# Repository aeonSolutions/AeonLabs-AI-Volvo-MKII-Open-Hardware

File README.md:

[ ](https://discord.gg/hw3j3RwfJf)

<p align="center">
    <br>

 &nbsp;

**[More Stats](https://github.com/aeonSolutions/AeonLabs-AI-Volvo-MKII-Open-Hardware/wiki/Project-Statistics)**
</p>

**Navigation** | [AeonLabs Main Index](https://github.com/aeonSolutions/aeonSolutions/blob/main/aeonSolutions-Main-Index.md)  >>  [Open Hardware Electronics](https://github.com/aeonSolutions/PCB-Prototyping-Catalogue)  >>   [Vehicle Automation](https://github.com/aeonSolutions/PCB-Prototyping-Catalogue/tree/main/Vehicle%20Automation)  >> Volvo P2 Open Hardware

<div align="right">
    
 <a href="https://github-com.translate.goog/aeonSolutions/AeonLabs-AI-Volvo-MKII-Open-Hardware/wiki?_x_tr_sl=en&_x_tr_tl=pt&_x_tr_hl=en&_x_tr_pto=wapp">Change language</a> <br>
 Last update: 24-06-2024
</div>

# Open Hardware Electronics for the Volvo P2 platform
**current project Total: > 1350 work.h** <br>
<sup>Status: Ongoing Project </sup> <br>
[where to buy](https://github.com/aeonSolutions/PCB-Prototyping-Catalogue/wiki/Where-to-Buy) already assembled and ready to use.

⚠️ This project is delayed because all my tools and equipment including all the Volvo P2 modules and wiring got stolen from my workplace and apartment ⚠️

**The problem** <br>
&nbsp; Nowadays, repairing hardware electronics is impossible or almost impossible. Current practice forces a car owner to replace instead of repair. This has a really high cost and pushes owners to seek other less trustworthy solutions using components used in other vehicles. Since this type of component is nowadays heavily protected, maintenance and repair outside the official car manufacturer authorized dealer to pose additional risks every time a piece of hardware electronics or firmware requires reverse engineering and modification just to enable it and make it work in another vehicle. Furthermore, recurrently found good, fully functional cars, with the highest safety classification rating on their chassis, the [Euro NCAP 5 star rating](https://www.euroncap.com/en/about-euro-ncap/how-to-read-the-stars/) being sent to the scrap yard due to outdated electronics and components and a too low insurance valuation that limits repairability of the vehicle.    

**Summary** <br>
The overall objective of this open project is to extend the life of vehicles by means of updating them to current EU standards namely safety regulations and emission pollutants. As so vehicles undergo a process of refurbishment service and full-featured overhaul of technology updates from mechanical key components to the interior habitacle, comfort, and safety of a vehicle. Branded **Auto RFTI™** (refurbishment, facelift, and technology improvements) goes a step further than just a vehicle facelift and will differentiate by offering simple & easy hardware electronics and components for extending vehicle utilization life by means of technology upgrades to improve safety while at the same time reduce vehicle emissions. 
- [The 6 Levels of Vehicle Autonomy](https://github.com/aeonSolutions/AeonLabs-AI-Volvo-MKII-Open-Hardware/wiki/The-6-Levels-of-Vehicle-Autonomy)
- [Milestones to Achieve for the Open Hardware Electronics](https://github.com/aeonSolutions/AeonLabs-AI-Volvo-MKII-Open-Hardware/wiki/Milestones-to-Achieve--for-the-Open-Hardware-Electronics)

<br>

In one sentence: 
<div align="center">

***"I'm solving all the electronics issues that make a P2 Volvo have a bad reputation"*** <br>

</div>

**Proof-of-Concept** <br>
&nbsp; Design and prototype OEM hardware electronics capable of the same operation and functionality for all Volvo's with the [common chassis P2](https://en.wikipedia.org/wiki/Volvo_P2_platform), period 1998 to 2009 (S80, S60, V70 XC70, XC90), using the existing wiring on those cars (backward compatible). Instead of using closed and protected logic, it uses open hardware and open firmware hardware electronics as a direct replacement for existing* wiring in a vehicle, in particular older cars. This will facilitate repeatability and maintenance on any "repair shop" outside authorized dealers and requires no reverse engineering and no modification to make it work in a vehicle.<br>

&nbsp; To achieve this task I will be using the electronics and electrical wiring of a donor car I already have. This will serve as a ground base to commercialize automotive solutions using an open business logic (open hardware and open software) for other car brands and models. Including LPG systems.

<div align="center">

***"still.... even if it is not easily possible ...it will definitely going to be AWESOME running a car <br> that will meet the latest EURO emissions except on the pink slip"*** <br>
<sup> <a href="https://discordapp.com/channels/879495735912071269/937480820594208808/1203010918833721446">Discord Server of Speeduino 02-02-2024 </a> </sup>
</div>

&nbsp; Since this is an open hardware project, the main selection of choice for the operating system will be Android Auto for the main LCD screen, in the center console. Nowadays there is a plenitude of "open auto" solutions using Raspberry Pi. I'll be designing the hardware electronics made to fit an SoC module, and I'll be starting with NVidia's Jetson Nano. In the following YouTube video, there's a good example of a traditional media unit https://www.youtube.com/watch?v=RgbHXTHUnQw <br>

Read more about ...
- [Open Hardware Design Considerations](https://github.com/aeonSolutions/AeonLabs-AI-Volvo-MKII-Open-Hardware/wiki/Open-Hardware-Design-Considerations)
- [Firmware Programming](https://github.com/aeonSolutions/AeonLabs-AI-Volvo-MKII-Open-Hardware/wiki/Firmware-Programming)

<br>

There are now 2 ways to navigate my hardware electronics catalog. The icons below will take you  to another page where this catalog is displayed using a conventional landing page design & styling. If you like code and more technical information, browse this page instead.
 
The icon to the left is suited to all those users who are only looking for a solution to a problem and not into the real technical details.  The icon to the right will take you directly to a webpage with all hardware electronics currently at the [M.V.P. stage](https://en.wikipedia.org/wiki/Minimum_viable_product). If you're not into technical information and are here only to buy, this is the option for you. 

<p align="center">
 
  &emsp;&emsp;&emsp;&emsp;&emsp;&emsp;&emsp;
   <br>
 <sup>View this repository in a conventional landing page</sup>
  &emsp;&emsp;&emsp;&emsp;&emsp;&emsp;&emsp;
 <sup> View all open hardware solutions ready to buy, install, and use</sup>
</p>

Make sure you also view my **Open Source Software Catalogue** [here](https://github.com/aeonSolutions/aeonlabs-open-software-catalogue). 

<br>

## What hardware electronics will be conceptualized, prototyped, and tested
&nbsp; The main objective of this project is to study the advantages of using open solutions and compare them with conventional hardware electronics solutions. In particular in regards to serviceability, maintenance, and repairability and also importantly, in regards to personal ownership safety. While driving and while parked (thieves). 

[continue reading ...](https://github.com/aeonSolutions/AeonLabs-AI-Volvo-MKII-Open-Hardware/wiki)

<br>

## Compatibility

<p align="center">

</p>

<br>

**Get a Notification on every PCB update**

|  | You can fill in your [email here (Google form)](https://docs.google.com/forms/d/e/1FAIpQLScErMgQYRdA-umvCjvTPPrCO7Lg1QYowTxb7vfa8cTfrcPEAA/viewform?usp=pp_url) and I'll send a reminder when a new PCB prototype is made available here or a new revision for an existing PCB. Stay tuned! |
|-------------|------|

<br>

**Hire AeonLabs** <br>
If you like my work here and are looking to design and deploy your own smart device find [here](https://github.com/aeonSolutions/PCB-Prototyping-Catalogue/wiki/How-to-Hire-AeonLabs) how to hire me. 

<br>

## Join the Beta Program
Join the beta program to test and debug to provide feedback, ideas, modifications, suggestions, and improvements. And in return, write your own article blog, or post on social media about it. See participation conditions on the [Wiki](https://github.com/aeonSolutions/PCB-Prototyping-Catalogue/wiki/Beta-Participation-Agreement).  

## Contributing

Bug reports and pull requests are welcome on any of AeonLabs repositories. This project is intended to be a safe, welcoming space for collaboration, and contributors are expected to adhere to the [code of conduct](https://github.com/aeonSolutions/OpenScience-Dataverse-API-C-library/blob/main/CODE_OF_CONDUCT.md).

- Contributing
  - [Your Contributions Matter](https://github.com/aeonSolutions/PCB-Prototyping-Catalogue/wiki/Your-Contributions-Matter)
  - [Contributor Code of Conduct](https://github.com/aeonSolutions/PCB-Prototyping-Catalogue/wiki/Contributor-Code-of-Conduct)

<br>

**[Beta Participation Agreement](https://github.com/aeonSolutions/PCB-Prototyping-Catalogue/wiki/Beta-Participation-Agreement)**

The Beta Participant Agreement is a legal document being executed between you and AeonLabs that outlines the conditions when participating in the Beta Program.

## Coding standards

Please make sure tests pass before committing, and add new tests for new additions.

- Licensing 
  - [AeonLabs Solutions for Open Hardware & Source Development](https://github.com/aeonSolutions/PCB-Prototyping-Catalogue/wiki/AeonLabs-Solutions-for-Open-Hardware-&-Source-Development)

<br>
<br>

## Author

You can get in touch with me on my LinkedIn Profile:

#### Miguel Tomas

You can also follow my GitHub Profile to stay updated about my latest projects: 

<br>

### Be supportive of my dedication and work towards technology education and buy me a cup of coffee
The PCB Design Files I provide here for anyone to use are free. If you like this Smart Device or use it, please consider buying me a cup of coffee, a slice of pizza, or a book to help me study, eat, and think new PCB design files.

<p align="center">
    
</p>

### Make a donation on Paypal
Make a donation on PayPal and get a TAX refund*.

<p align="center">
    
</p>

### Support all these open hardware projects and become a GitHub sponsor  
Did you like any of my PCB KiCad Designs? Help and Support my open work to all by becoming a Github sponsor.

<p align="center">

</p>

## License

Before proceeding to download any of AeonLab's open-source code for software solutions and/or open hardware electronics for smart devices and data acquisition make sure you are choosing the right license for your project. See [AeonLabs Solutions for Open Hardware & Open Source Code](https://github.com/aeonSolutions/aeonSolutions/wiki/AeonLabs-Licensing) for more information. For commercial business solutions contact AeonLabs ℹ️ using the contacts above. Thank you 🙏.

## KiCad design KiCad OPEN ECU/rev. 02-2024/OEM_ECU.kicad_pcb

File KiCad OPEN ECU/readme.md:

[Main Page](https://github.com/aeonSolutions/AeonLabs-AI-Volvo-MKII-Open-Hardware/wiki)  >>  KiCad project files for the OPEN ECU

<div align="right">
 <a href="https://github-com.translate.goog/aeonSolutions/AeonLabs-AI-Volvo-MKII-Open-Hardware/wiki?_x_tr_sl=en&_x_tr_tl=pt&_x_tr_hl=en&_x_tr_pto=wapp">Change language</a>  <br>
Last change 09-04-2024
</div>

<br>

This folder contains the KiCad Project files, for the hardware electronics of the OPEN ECU.  Each KiCad project is available with a [creative commons share alike non-commercial license](https://creativecommons.org/licenses/by-nc-sa/4.0/deed.en). 

<p align="center">
  <strong> <a href="https://aeonsolutions.github.io/portfolio/hardware_electronics/automotive/">Interactive web view of the PCB Layout</a> </strong> <br>
 <sup>Click to view the latest revision of the PCB Layout</sup>
</p>

However, they're not fully complete. If you like it and are looking to use it on your projects, you can download the complete Kicad project files with a one-time donation, [click here](https://github.com/sponsors/aeonSolutions) to learn how,  and don't forget to include it in a message the name of the module/hardware electronics you need. <br> Thank you 🙏.

### Support all these open hardware projects and become a GitHub sponsor  
Did you like any of my PCB KiCad Designs? Help and Support my open work to all by becoming a GitHub sponsor.

<p align="center">

</p>

#

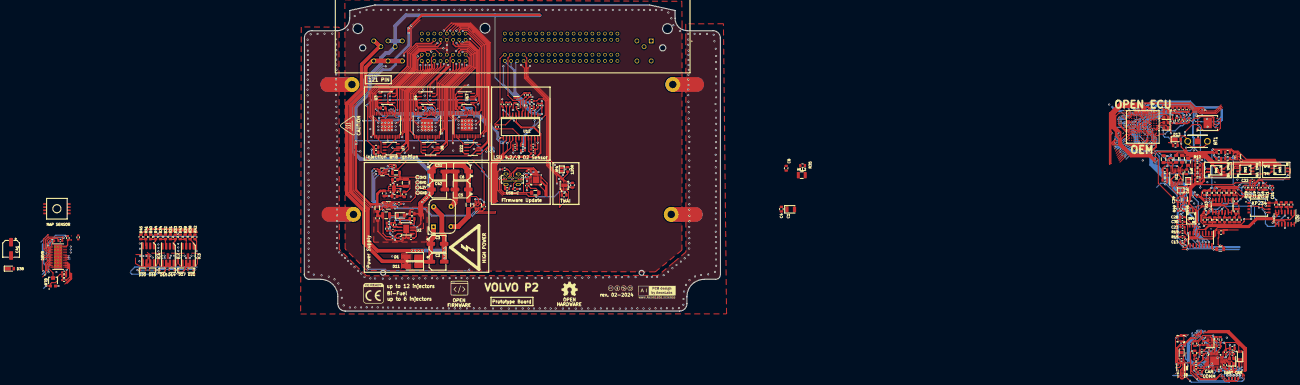
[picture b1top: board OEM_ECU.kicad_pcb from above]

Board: 2 copper layers, 168.9 x 124.3 mm, 246 parts (1 on the bottom side), 206 nets.

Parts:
AUC1: 100nF; C_0603_1608Metric
AUR1: AUR9718x_DFN_3x3mm_6_pin; AUR9718 ST1S09 SON95P300X300X100-7N
AUR_C1: 22uF; C_0805_2012Metric_Pad1.18x1.45mm_HandSolder
AUR_C2: 4.7uF; C_0805_2012Metric_Pad1.18x1.45mm_HandSolder
AUR_R1: 24k; R_0805_2012Metric_Pad1.20x1.40mm_HandSolder
AUR_R2: 75k; R_0805_2012Metric_Pad1.20x1.40mm_HandSolder
AUR_l1: 3.3uF; L_1210_3225Metric
BT1: Battery_Cell; pcb battery 3 pin
C1, C7, C8, C8#2, C11, C12, C16, C17, C27, C33, C37: 0.1uF; C_0805_2012Metric
C2, C42: 100pF; CP_Elec_6.3x7.7
C3, C5, C6: 10uF; CP_Elec_6.3x7.7
C4: 47uF; CP_EIA-3528-21_Kemet-B
C10, C26, C38: 1uF; C_0805_2012Metric
C13, C23: 270nF; C_0603_1608Metric
C14, C15, C20: 0.22uF; C_0805_2012Metric
C18, C19, C29: 0.1uF; C_0603_1608Metric
C21, C22: 0.22uF; C_0603_1608Metric
C24: 100uF; C_1206_3216Metric
C25, C35, C39, C40: 0.01uF; C_0805_2012Metric
C28: 0.01uF; C_0603_1608Metric
C30: 4700pF; C_0603_1608Metric
C32: 4.7uF; CP_Elec_6.3x7.7
C34, C36: 1nF; C_0805_2012Metric
C41: 100uF; CP_Elec_6.3x7.7
CHC1, CHC2, CHC3: 1uF; C_0603_1608Metric
CJC1: 2.2nF; C_0603_1608Metric
CJC2, CJC3, CJC4, CJC5, CJC6: 100nF; C_0603_1608Metric
CJC7, CJC8: 33nF; C_0603_1608Metric
CJQ1: AO3400A; SOT-23
CJR1: 61R9; R_0603_1608Metric
CJR2: 10K; R_0603_1608Metric
CJR3: 300R; R_0603_1608Metric
CJR4: 31K6; R_0603_1608Metric
CJR5, CJR11: 4K7; R_0603_1608Metric
CJR6, CJR8, CJR10: 100K; R_0603_1608Metric
CJR7: 470K; R_0603_1608Metric
CJR9: 6K8; R_0603_1608Metric
D1, D11: SS36; D_SMA_Handsoldering
D13, D38: D_Schottky; D_PowerDI-123
D14, D15, D16, D17, D20, D21: D; D_SOD-323
DRV8: DRV8825PWPR
DRVC1: 10nF; C_0603_1608Metric
DRVC2: 100nF; C_0603_1608Metric
DRVC3: 0.47uF; C_0603_1608Metric
DRVR1: 1K5; R_0603_1608Metric
DRVR2: 10K; R_0603_1608Metric
DRVR3, DRVR4: 0.10R; R_0603_1608Metric
EC1, EC8, EC9, EC14, EC15, EC17: 100nF; C_0603_1608Metric
EC2, EC3, EC4, EC5: 22pF; C_0603_1608Metric
EC6, EC7: 10uF; C_0805_2012Metric
EC16: 1uF; C_0805_2012Metric
ECY1: 32.768Mhz; Crystal_SMD_3225-4Pin_3.2x2.5mm
ECY2: 40Mhz; Crystal_SMD_3225-4Pin_3.2x2.5mm
ER1, ER3: 10k; R_0603_1608Metric
ER2: 499R; R_0603_1608Metric
ER4, ER5, ER6: 1R; R_1206_3216Metric
ESP_FLASH1: W25Q32JVUXIQ; WSON8 FLASH SPI SON127P800X600X80-9N
HLL1: SQ1010_8x5mm; Common Mode Inductor SQ1010 8x5mm
HLL2: 6.8uH; L_1210_3225Metric
IC1: MAX9926UAEE_V+; QSOP-16_3.9x4.9mm_P0.635mm
IC2, IC3, IC4: ZXMS6006DT8; Diodes_SM8
IMU2: LSM6DS3; LSM6DS3 Motion Sensor PQFN50P300X250X86-14N
INA1, INA4, INA5: INA219AIDCNR; INA219AIDCNR SOT65P280X145-8N
INA1_C1, INA1_C4, INA1_C5: 100nF; C_0603_1608Metric
J3: USB4120-03-C_REVA; USB-C Vertical GCT_USB4120-03-C_REVA
JP2, JP3: Jumper_2_Open; SolderJumper-2_P1.3mm_Open_Pad1.0x1.5mm
JP4: Jumper_NO_Small; SolderJumper-2_P1.3mm_Open_Pad1.0x1.5mm
L1: 2nH; L_0805_2012Metric
LED1: LED_GBRC; LED_1206_3210_RGB_Metric
LR1: 330R; R_0603_1608Metric
MCU1: MK64FX512VMD12; NXP 144 PIN BGA
MKC1, MKC6: 2.2uF; C_0603_1608Metric
MKC2, MKC3: 10nF; C_0603_1608Metric
MKC4, MKC5, MKC7: 100nF; C_0603_1608Metric
MKCY1: 16mHz; Crystal_SMD_3225-4Pin_3.2x2.5mm
MKCY2: 32.768MHz; Crystal_SMD_3225-4Pin_3.2x2.5mm
MKL1, MKL2: FER 600; L_0805_2012Metric
MKR1: 470R; R_0603_1608Metric
MPC1: 10uF; C_0805_2012Metric
MPC2: 100Nf; C_0805_2012Metric
MPC3: 220PF; C_0603_1608Metric
MPC4: 22UF; C_0805_2012Metric
MPD1: SS12; D_1206_3216Metric
MPL1: 10uF; L_1210_3225Metric
MPR1: 24.9K; R_0603_1608Metric
MPR2: 100k; R_0603_1608Metric
MPR3: 200K; R_0603_1608Metric
MPR4: 68.1K; R_0603_1608Metric
MPR5: 40.2K; R_0603_1608Metric
MPR6: 124K; R_0603_1608Metric
PWR_FUSE1: Polyfuse; Fuse_1206_3216Metric_Pad1.42x1.75mm_HandSolder
Q2, Q3: Q_DUAL_NMOS_S1G1D2S2G2D1; SOT-363_SC-70-6
R1, R5, R6, R35: 10k; R_0805_2012Metric
R2: 120R; R_0805_2012Metric
R11: 604R; R_0805_2012Metric
R12: 3.88k; R_0603_1608Metric
R13, R14, R20: 470R; R_0805_2012Metric
R15: 2.4k; R_0603_1608Metric
R17, R18: 2.49k; R_0603_1608Metric
R19, R48, R49: 1k; R_0603_1608Metric
R21, R22: 470R; R_0603_1608Metric
R23, R24, R29, R46, R55, R57: 180k; R_0805_2012Metric
R25, R26, R30, R47, R56, R58: 348k; R_0805_2012Metric
R27, R36, R37, R59: 10k; R_1206_3216Metric
R28: 0; R_0805_2012Metric
R31, R32, R38, R39, R40, R41, R60, R61, R69: 1k; R_0805_2012Metric
R33, R34, R42, R43, R44, R45: 100k; R_0805_2012Metric
R70: TC33X-2-503G; Trimmer potentiometer 3x3mm _TC33X-2-503G
SW1, SW2, SW3, SW4: 219-2MSTR; Dip Switch 2 toggle
TP1: VOut; TestPoint_Pad_D1.0mm
TP2: GND; TestPoint_Pad_D1.0mm
TP3: VIN; TestPoint_Pad_D1.0mm
TP4: 12V; TestPoint_Pad_D1.0mm
U1: ESP32C3; ESP32 C3 QFN32_5X5MM
U2: MP1584EN; MP1584EN SOIC127P600X170-9N
U3, U4, U7, U8, U17, U22: TC4424A; SOIC-8_3.9x4.9mm_P1.27mm
U5, U6, U18: MC33810; mc33810 SOIC32-P0.65-33N
U9: BMP280; XDCR_BMP280
U10: SP720; SOIC-16_3.9x9.9mm_P1.27mm
U11: KP234; kp234 barometric sensor
U12: CJ125; CJ125 Wideband sensor
U13, U20: LMV324LIDT; SOIC-14_3.9x8.7mm_P1.27mm
U14: MPXH6400A; NXP MAP Sensor
U15: 121 pin ECU connector header
U16: ATSHA204A-MAHDA-T; ATSHA204A-MAHDA-T UDFN-8
U21: AHT20; AHT20 PSON100P300X300X110-6N
U23: CH9102F
U24: MCP2562-E_MF; MCP2562 DFN
UART_CON1: UART_CONN; SOIC_clipProgSmall
USB_PLUG_R3, USB_PLUG_R4: 5k1; R_0603_1608Metric
USB_PLYG_R2: 150K; R_0603_1608Metric

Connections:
3V3_PROBE_IN: AUR_C1.1, AUR_R2.1, AUR_l1.1, ER6.2, INA5.1 (IN+), TP1.1
5V_PROBE_IN: ER5.1, INA4.1 (IN+), MPC4.1, MPL1.2, MPR6.2
12V-BAT: D1.2 (A), D11.2 (A), U15.116, U15.118
12V-SW: C8.1, D14.1 (K), D15.1 (K), D16.1 (K), D17.1 (K), D20.1 (K), D21.1 (K), D38.2 (A), R12.2, R35.2
12V_PROBE_IN: ER4.1, HLL1.2, INA1.1 (IN+)
+3.3V: CHC3.1, U23.5 (VIO)
+3V3: AUC1.2, C8#2.1, C24.2, D13.2 (A), DRV8.15 (V3P3OUT), DRV8.16 (~NRESET), DRV8.17 (NSLEEP), DRVC3.1, DRVR2.2, EC6.1, EC7.1, EC9.1, EC14.1, EC15.1, EC16.2, EC17.2, ER1.1, ER3.1, ER6.1, ESP_FLASH1.3 (IO2), ESP_FLASH1.7 (IO3), ESP_FLASH1.8 (VCC), IMU2.5 (VDDIO), IMU2.8 (VDD), INA1.4 (VS), INA1.8 (A1), INA1_C1.2, INA1_C4.2, INA1_C5.2, INA4.4 (VS), INA4.8 (A1), INA5.2 (IN-), INA5.4 (VS), INA5.7 (A0), INA5.8 (A1), L1.1, LED1.4 (K), MCU1.E5 (VDD), MCU1.E6 (VDD), MCU1.E7 (VDD), MCU1.E8 (VDD), MCU1.F5 (VDD), MCU1.F8 (VDD), MCU1.G1 (VOUT33), MKC1.2, MKC2.2, MKC3.2, MKC4.2, MKL1.2, Q2.2 (G), Q2.5 (G), Q3.2 (G), Q3.5 (G), R15.1, R17.2, R18.2, R19.2, R48.2, R49.1, R60.2, R61.2, R70.1, U1.11 (VDD3P3_RTC), U1.17 (VDD3P3_CPU), U1.31 (VDDA), U1.32 (VDDA__1), U5.8 (VDD), U6.8 (VDD), U9.2 (CSB), U9.6 (VDDIO), U9.8 (VDD), U10.16 (V+), U16.8 (VCC), U18.8 (VDD), U21.2 (VDD), U24.5 (VIO), UART_CON1.1
+5V: AUR1.4 (VIN_SW), AUR1.5 (VIN_A), AUR1.6 (EN), AUR_C2.1, C1.1, C4.1, C7.2, C33.2, C35.1, C37.1, C38.1, CHC1.1, CJC3.2, CJC4.2, ER5.2, IC1.14 (VCC), INA4.2 (IN-), PWR_FUSE1.1, TP3.1, U5.25 (VPWR), U6.25 (VPWR), U12.17 (VCC), U18.25 (VPWR), U23.7 (VDD5), U23.8 (VBUS), U24.3 (VDD)
+12V: C5.1, C6.1, C10.1, C16.1, C32.1, C42.1, CJC5.2, ER4.2, HLL2.1, INA1.2 (IN-), MPC1.1, MPR1.1, MPR2.1, MPR2.2, TP4.1, U2.2 (EN), U2.7 (VIN), U3.6 (VDD), U4.6 (VDD), U7.6 (VDD), U8.6 (VDD), U12.1 (UB), U15.114, U15.115, U15.117, U17.6 (VDD), U22.6 (VDD)
ADC2_CH0: EC4.1, ECY1.1, U1.5 (XTAL_32K_N)
ADC-Clamp-3: U10.3 (I3), U20.6 (-), U20.7
ADC-Clamp-4: U10.4 (I4), U20.1, U20.2 (-)
ADC-Clamp-5: C13.1, MCU1.E11 (PTB11), R15.2, U10.5 (I5)
ADC-Clamp-6: C23.1, MCU1.E12 (PTB10), R19.1, U10.6 (I6)
ADC-Clamp-7: C15.1, MCU1.D11 (PTB19), R14.1, U10.7 (I7)
ADC-Clamp-11: C21.1, MCU1.A8 (PTC8), R21.1, U10.12 (I11)
ADC-Clamp-12: C22.1, MCU1.D7 (PTC9), R22.1, U10.13 (I12)
ADC-Clamp-13: MCU1.C7 (PTC10), U10.14 (I13), U13.8, U13.9 (-)
ADC-Clamp-14: MCU1.B7 (PTC11/LLWU_P11), U10.15 (I14), U13.13 (-), U13.14
BARO-5V: C27.2, R23.2, R28.2
BOOST-OUT: D20.2 (A), IC4.5 (DRAIN_2_1), IC4.6 (DRAIN_2_2)
CAM-IN+: SW2.1A, SW2.2A
CAN_H: JP4.1, U15.9, U24.7 (CANH)
CAN_L: R2.1, U15.28, U24.6 (CANL)
CAN_RXD: U1.9 (MTMS), U24.4 (RXD)
CAN_TXD: U1.13 (MTDO), U24.1 (TXD)
CHIP_EN: EC1.2, ER1.2, U1.7 (CHIP_EN), U23.18 (CTS), UART_CON1.6
CLT_Sensor: C19.1, R18.1, R22.2
CRANK-IN+: SW1.1A, SW1.2A
DIAHD: CJR9.1, U12.7 (DIAHD)
DIAHG: CJR11.2, U12.6 (DIAHG)
ESP32_I2C_SCL: IMU2.13 (SCL), MCU1.M4 (PTE24), U1.12 (MTCK), U9.4 (SCK), U16.6 (SCL), U21.3 (SCL)
ESP32_I2C_SDA: IMU2.14 (SDA), MCU1.K5 (PTE25), U1.10 (MTDI), U9.3 (SDI), U16.5 (SDA), U21.4 (SDA)
ESP_GPIO0_BOOT-DTR: ER3.2, U1.15 (GPIO9), U23.23 (DTR), UART_CON1.5
FAN-OUT: D16.2 (A), IC4.7 (DRAIN_1_1), IC4.8 (DRAIN_1_2)
FAULT: DRVR1.2, DRVR2.1
GND: AUC1.1, AUR1.2 (GND), AUR1.7 (GND), AUR_C1.2, AUR_C2.2, AUR_R1.2, BT1.2 (-), C1.2, C4.2, C5.2, C6.2, C7.1, C8.2, C8#2.2, C10.2, C11.2, C12.2, C13.2, C14.2, C15.2, C16.2, C17.2, C18.2, C19.2, C20.2, C21.2, C22.2, C23.2, C24.1, C25.1, C26.1, C27.1, C28.1, C29.1, C30.2, C32.2, C33.1, C35.2, C37.2, C38.2, C39.1, C40.1, C41.2, C42.2, CHC1.2, CHC2.1, CHC3.2, CJC1.1, CJC3.1, CJC4.1, CJC5.1, CJC6.1, CJC7.1, CJC8.1, CJQ1.2 (S), CJR2.1, CJR10.2, DRV8.14 (GND), DRV8.28 (GND__1), DRV8.29 (GND__PAD), DRVC3.2, DRVR3.1, DRVR4.1, EC1.1, EC2.2, EC3.2, EC4.2, EC5.2, EC6.2, EC7.2, EC8.2, EC9.2, EC14.2, EC15.2, EC16.1, EC17.1, ECY1.2, ECY1.4, ECY2.2, ECY2.4, ESP_FLASH1.4 (GND), ESP_FLASH1.9 (GND), HLL1.4, IC1.1 (IN_THRS1), IC1.3 (BIAS1), IC1.6 (BIAS2), IC1.8 (INT_THRS2), IC1.11 (GND), IC1.13 (ZERO_EN), IC2.2 (SOURCE_1), IC2.4 (SOURCE_2), IC3.2 (SOURCE_1), IC3.4 (SOURCE_2), IC4.2 (SOURCE_1), IC4.4 (SOURCE_2), IMU2.6 (GND), IMU2.7 (GND), INA1.3 (GND), INA1.7 (A0), INA1_C1.1, INA1_C4.1, INA1_C5.1, INA4.3 (GND), INA5.3 (GND), J3.A1 (GND_A), J3.A12 (GND_A__1), J3.B1 (GND_B), J3.B12 (GND_B__1), MCU1.F6 (VSS), MCU1.F7 (VSS), MCU1.G7 (VSS), MCU1.G8 (VSS), MCU1.H3 (VSS), MCU1.H7 (VSS), MCU1.H8 (VSS), MCU1.M10 (VSS), MKC1.1, MKC2.1, MKC3.1, MKC4.1, MKCY1.2, MKCY1.4, MKCY2.2, MKCY2.4, MKL2.1, MPC1.2, MPC4.2, MPD1.2 (A), MPR1.2, MPR3.2, MPR4.2, MPR5.2, R1.2, R5.2, R6.2, R11.1, R25.1, R26.1, R30.1, R33.2, R34.1, R42.2, R43.1, R44.2, R45.1, R47.1, R56.1, R58.1, R70.3, TP2.1, U1.33 (GND), U2.5 (GND), U2.9 (GND), U3.3 (GND), U4.3 (GND), U5.33 (GND), U6.33 (GND), U7.3 (GND), U8.3 (GND), U9.1 (GND), U9.5 (SDO), U9.7 (GND), U10.8 (GND), U11.6 (GND), U11.8 (GND), U12.24 (GND), U13.11 (V-), U14.3 (GND), U15.93, U15.101, U16.4 (GND), U17.3 (GND), U18.33 (GND), U20.11 (V-), U21.5 (GND), U22.3 (GND), U23.0 (GND), U23.2 (GND), U24.2 (VSS), U24.9 (EPAD), UART_CON1.2, USB_PLUG_R3.2, USB_PLUG_R4.2, USB_PLYG_R2.2
GND-BAT: C2.2, C3.2, HLL1.3, U15.119, U15.120, U15.121
GNDA: MCU1.G6 (VREFL), MCU1.H6 (VSSA), MKC5.1, MKC6.1, MKC7.1, MKL2.2
GPIO8_I2C_SDA: INA1.6 (SDA), INA4.6 (SDA), INA4.7 (A0), INA5.6 (SDA)
GPIO9_I2C_SCL: INA1.5 (SCL), INA4.5 (SCL), INA5.5 (SCL)
IAT_Sensor: C18.1, R17.1, R21.2
IDLE-OUT: D14.2 (A), DRV8.10 (BOUT1), IC2.7 (DRAIN_1_1), IC2.8 (DRAIN_1_2)
IGN1: U3.5 (OUT_B), U15.102
IGN2: U3.7 (OUT_A), U15.104
IGN3: U7.7 (OUT_A), U15.112
IGN4: U7.5 (OUT_B), U15.103
IGN5: U4.5 (OUT_B), U15.109
IGN6: U4.7 (OUT_A), U15.100
IGN7: U8.7 (OUT_A), U15.106
IGN8: U8.5 (OUT_B), U15.98
IGN9: U15.90, U17.5 (OUT_B)
IGN10: U15.91, U17.7 (OUT_A)
IGN11: U15.84, U22.7 (OUT_A)
IGN12: U15.85, U22.5 (OUT_B)
INJ1: U5.17 (OUT3), U15.95
INJ2: U5.16 (OUT1), U15.94
INJ3: U5.1 (OUT0), U15.105
INJ4: U5.32 (OUT2), U15.113
INJ5: U6.17 (OUT3), U15.111
INJ6: U6.16 (OUT1), U15.110
INJ7: U6.1 (OUT0), U15.108
INJ8: U6.32 (OUT2), U15.107
INJ9: U15.99, U18.17 (OUT3)
INJ10: U15.92, U18.16 (OUT1)
INJ11: U15.82, U18.1 (OUT0)
INJ12: U15.83, U18.32 (OUT2)
LED_B_IO05: LED1.2 (BA), U1.19 (SPIHD)
LED_G_IO02: LED1.1 (GA), U1.20 (SPIWP)
LED_R_IO04: LR1.1, U1.23 (SPID)
LSU_HEAT-: CJQ1.3 (D), CJR9.2, U15.26
LSU_IA: CJR1.1, CJR7.2, U12.4 (IA), U15.7
LSU_IP: CJR1.2, U12.3 (IP), U15.8
LSU_UN: CJC1.2, CJR6.2, U12.2 (UN), U15.6
LSU_VM: CJR3.2, U12.18 (VM), U15.25
MAP-5V: R29.2, SW3.1B, SW3.2B
MC33810_1-CS: MCU1.B8 (PTC7), U5.4 (CS)
MC33810_2-CS: MCU1.C8 (PTC6/LLWU_P10), U6.4 (CS)
MC33810_3-CS: MCU1.B12 (PTC0), U18.4 (CS)
MCU-A0: MCU1.H11 (PTA29), U13.1, U13.2 (-)
MCU-A1: MCU1.J11 (PTA26), U13.6 (-), U13.7
MCU-A4: C29.2, IC1.5 (COUT2), JP3.1 (A), MCU1.C11 (PTB23), Q2.4 (S), R49.2
MCU-A5: IC1.4 (COUT1), JP2.2 (B), MCU1.D9 (PTB21), Q2.1 (S), R48.1, SW4.1A, SW4.2A
MCU-A8: C40.2, MCU1.G10 (PTB4), Q3.4 (S), R61.1
MCU-A9: C39.2, MCU1.G9 (PTB5), Q3.1 (S), R60.1
MCU-AREF: MCU1.G5 (VREFH), MKC5.2, MKR1.1
MCU-D6: ESP_FLASH1.1 (~CS), MCU1.B4 (PTD3)
MCU-D24: MCU1.H10 (PTB0/LLWU_P5), R41.2
MCU-D25: MCU1.H9 (PTB1), R40.2
MCU-D26: MCU1.G11 (PTB3), R32.2
MCU-D27: MCU1.G12 (PTB2), R31.2
MCU-D28: MCU1.A3 (PTD5), R39.2
MCU-D29: MCU1.A2 (PTD6/LLWU_P15), R38.2
MCU-D30: DRV8.21 (NENBL), MCU1.B11 (PTC1/LLWU_P6)
MCU-D31: DRV8.22 (STEP), MCU1.A12 (PTC2)
MCU-D32: DRV8.20 (DIR), MCU1.K4 (PTE26)
MCU-VDDA: MCU1.H5 (VDDA), MKC6.2, MKL1.1, MKR1.2
MCU-VREF_OUT: MCU1.M3 (VREF_OUT/CMP1_IN5/CMP0_IN5/ADC1_SE18), MKC7.2
MCU_UART0_CTS: MCU1.J5 (PTA0), U1.8 (GPIO3)
MCU_UART0_RX: MCU1.J6 (PTA1), U1.6 (GPIO2)
MCU_UART0_TX: MCU1.K6 (PTA2), U1.16 (GPIO10)
MCU_UART_RTS_RST: MCU1.K7 (PTA3), MCU1.L12 (RESET_B), U1.14 (GPIO8)
MCU_VBAT: BT1.1 (+), MCU1.L6 (VBAT), R69.1
MISO: ESP_FLASH1.2 (DO(IO1)), MCU1.D4 (PTD1), U5.7 (SO), U6.7 (SO), U12.14 (MISO), U18.7 (SO)
MOSI: ESP_FLASH1.5 (DI(IO0)), MCU1.D8 (PTC5/LLWU_P9), U5.6 (SI), U6.6 (SI), U12.15 (MOSI), U18.6 (SI)
unnamed: AUR1.1 (FB), AUR_R1.1, AUR_R2.2
unnamed: AUR1.3 (SW), AUR_l1.2
unnamed: C12.1, R11.2, R12.1, R14.2
unnamed: C28.2, SW4.1B
unnamed: C30.1, SW4.2B
unnamed: CJC2.2, CJR4.2
unnamed: CJQ1.1 (G), CJR10.1, CJR11.1
unnamed: C2.1, C3.1, D1.1 (K), D11.1 (K), HLL1.1
unnamed: D13.1 (K), R69.2
unnamed: DRV8.12 (AVREF), DRV8.13 (BVREF), R70.2
unnamed: DRV8.1 (CP1), DRVC1.2
unnamed: DRV8.2 (CP2), DRVC1.1
unnamed: DRV8.6 (ISENA), DRVR4.2
unnamed: DRV8.9 (ISENB), DRVR3.2
unnamed: DRV8.18 (NFAULT), DRVR1.1
unnamed: DRV8.3 (VCP), DRVC2.1
unnamed: C34.1, IC1.16 (IN1+), R27.2
unnamed: C34.2, IC1.15 (IN1-), R36.2
unnamed: C36.2, IC1.9 (IN2+), R59.2
unnamed: C36.1, IC1.10 (IN2-), R37.2
unnamed: IC2.1 (INPUT_1), R31.1, R33.1
unnamed: IC2.3 (INPUT_2), R32.1, R34.2
unnamed: IC3.1 (INPUT_1), R38.1, R42.1
unnamed: IC3.3 (INPUT_2), R39.1, R43.2
unnamed: IC4.1 (INPUT_1), R40.1, R44.1
unnamed: IC4.3 (INPUT_2), R41.1, R45.2
unnamed: J3.A5 (CC1), USB_PLUG_R3.1
unnamed: J3.B5 (CC2), USB_PLUG_R4.1
unnamed: J3.S1 (SHIELD), USB_PLYG_R2.1
unnamed: JP2.1 (A), Q2.6 (D), SW1.1B
unnamed: JP3.2 (B), Q2.3 (D), SW2.2B
unnamed: JP4.2, R2.2
unnamed: LED1.3 (RA), LR1.2
unnamed: MCU1.M6 (EXTAL32), MKCY2.1
unnamed: MCU1.M12 (PTA18), MKCY1.3
unnamed: MCU1.M11 (PTA19), MKCY1.1
unnamed: MCU1.M7 (XTAL32), MKCY2.3
unnamed: MPC3.2, MPR4.1
unnamed: MPC2.1, MPD1.1 (K), MPL1.1, U2.1 (SW)
unnamed: ER2.2, U1.28 (U0TXD)
unnamed: EC8.1, L1.2, U1.2 (VDD3P3), U1.3 (VDD3P3__1)
unnamed: EC5.1, ECY2.1, U1.29 (XTAL_N)
unnamed: EC3.1, ECY2.3, U1.30 (XTAL_P)
unnamed: MPC2.2, U2.8 (BST)
unnamed: MPC3.1, U2.3 (COMP)
unnamed: MPR5.1, MPR6.1, U2.4 (FB)
unnamed: MPR3.1, U2.6 (FREQ)
unnamed: U3.2 (IN_A), U5.14 (GD1)
unnamed: U3.4 (IN_B), U5.3 (GD0)
unnamed: U4.2 (IN_A), U6.14 (GD1)
unnamed: U4.4 (IN_B), U6.3 (GD0)
unnamed: U5.30 (GD2), U7.2 (IN_A)
unnamed: U5.19 (GD3), U7.4 (IN_B)
unnamed: U6.30 (GD2), U8.2 (IN_A)
unnamed: U6.19 (GD3), U8.4 (IN_B)
unnamed: R28.1, U11.7 (Vout)
unnamed: CJC6.2, CJR8.1, U12.22 (CF)
unnamed: CJC2.1, U12.11 (CM)
unnamed: CJR2.2, U12.5 (OSZ)
unnamed: CJR8.2, U12.23 (RF)
unnamed: CJR4.1, U12.10 (RM)
unnamed: CJR3.1, U12.9 (RS)
unnamed: CJR5.2, CJR6.1, CJR7.1, U12.20 (UP)
unnamed: CJR5.1, U12.19 (US)
unnamed: R23.1, R25.2, U13.3 (+)
unnamed: R29.1, R30.2, U13.5 (+)
unnamed: R24.1, R26.2, U13.10 (+)
unnamed: R46.1, R47.2, U13.12 (+)
unnamed: SW3.2A, U14.4 (VOUT)
unnamed: U17.2 (IN_A), U18.14 (GD1)
unnamed: U17.4 (IN_B), U18.3 (GD0)
unnamed: U18.30 (GD2), U22.2 (IN_A)
unnamed: U18.19 (GD3), U22.4 (IN_B)
unnamed: R55.1, R56.2, U20.3 (+)
unnamed: R57.1, R58.2, U20.5 (+)
unnamed: U20.8, U20.9 (-)
unnamed: U20.13 (-), U20.14
unnamed: CHC2.2, U23.6 (V3)
O2-5V: C14.1, R13.1, R24.2
O2_Sensor: C11.1, R13.2
OUTEN_1: R5.1, U5.9 (OUTEN)
OUTEN_2: R6.1, U6.9 (OUTEN)
OUTEN_3: R1.1, U18.9 (OUTEN)
RXD0: U1.27 (U0RXD), U23.19 (RTS), UART_CON1.4
SCLK: ESP_FLASH1.6 (CLK), MCU1.H12 (PTA28), U5.5 (SCLK), U6.5 (SCLK), U12.13 (SCK), U18.5 (SCLK)
SPARE1-OUT: D21.2 (A), DRV8.7 (AOUT2), IC3.7 (DRAIN_1_1), IC3.8 (DRAIN_1_2)
SPARE2-OUT: D15.2 (A), DRV8.8 (BOUT2), IC2.5 (DRAIN_2_1), IC2.6 (DRAIN_2_2)
STEPPER-A1: D17.2 (A), DRV8.5 (AOUT1), IC3.5 (DRAIN_2_1), IC3.6 (DRAIN_2_2)
TPS-5V: C20.1, R20.1, R46.2
TPS_Sensor: C17.1, R20.2
TXD0: ER2.1, U23.20 (RXD), UART_CON1.3
UA: CJC7.2, U12.21 (UA)
UR: CJC8.2, U12.12 (UR)
USB_5V0F: J3.A4 (VBUS_A), J3.A9 (VBUS_A__1), J3.B4 (VBUS_B), J3.B9 (VBUS_B__1), PWR_FUSE1.2
USB_D+: J3.A6 (D1+), J3.B6 (D2+), U1.26 (GPIO19), U23.3 (D+)
USB_D-: J3.A7 (D1-), J3.B7 (D2-), U1.25 (GPIO18), U23.4 (D-)
VDDA: C25.2, C26.2, U11.5 (Vcc), U13.4 (V+), U14.2 (VS), U20.4 (V+)
VMM: C41.1, D38.1 (K), DRV8.4 (VMA), DRV8.11 (VMB), DRVC2.2
VR1-IN+: R27.1, SW1.2B
VR2-IN+: R59.1, SW2.1B
XTAL_32K_P: EC2.1, ECY1.3, U1.4 (XTAL_32K_P)

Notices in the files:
KiCad OPEN ECU/rev. 02-2024/OEM_ECU.kicad_pcb:
Creative Commons non commercial share alike
